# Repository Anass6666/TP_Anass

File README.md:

# TP_Anass

1.1.6 Activation de l’USART2 en mode Asynchrone : Le baud rate est réglé à 115200 bits/s par défaut.

1.2.13 Rôle de PB9 : PB9 est relié à la masse à travers une résistance pull-down. Ceci garantit que la broche reste à un niveau logique bas (0V) lorsque non connectée, évitant ainsi les états indéfinis.

1.2.14 Rôle de L1, C5 et C7 : L1 agit comme un filtre contre le bruit de haute fréquence, tandis que C5 et C7 agissent comme des condensateurs de découplage pour filtrer une large gamme de fréquences de bruit et assurer une alimentation propre et stable pour le microcontrôleur.

1.3.3 Page indiquant les valeurs des condensateurs : Les valeurs des condensateurs sont disponibles sur la page 3 du datasheet "buxxsd5wg-e".

1.3.5 Page indiquant les valeurs de condensateurs : Les valeurs des condensateurs sont répertoriées sur la page 15 du datasheet "22244B-54643".

1.3.6 Rôle de la broche CS : La broche CS est utilisée pour activer et désactiver le dispositif DAC, permettant au microcontrôleur de communiquer avec le DAC lorsque la broche est basse.

1.3.7 Rôle de la broche LDAC : La broche LDAC contrôle le moment où la sortie du DAC est mise à jour, permettant une mise à jour synchronisée de la sortie du DAC.

1.3.8 Non-utilisation du signal MISO : Le signal MISO n'est pas utilisé car le DAC est unidirectionnel et ne nécessite que des données entrantes du microcontrôleur.

1.3.10 Où trouver les indications du pinout du connecteur SWD : Les indications sont disponibles sur le lien suivant : Connecter votre débogueur.

1.4.3 Signification de 0805, 0603, 1206 : Ces chiffres font référence aux dimensions des composants électroniques en montage en surface (SMD).

1.4.4 Signification de LQFP, SOT-223, SOIC : Ces sigles désignent différents types de boîtiers utilisés pour les composants électroniques, chacun ayant ses propres caractéristiques.

3.1.4 Signification de __STATIC_INLINE : Cette directive indique au compilateur de remplacer les appels de fonction par le contenu de la fonction.

3.1.5 Présence de code dans un fichier .h : Si une fonction INLINE est définie dans un fichier d'en-tête, elle est copiée dans le fichier source lors de la compilation.

3.2.2 Valeur du prescaler : Le prescaler est réglé à 64 pour obtenir une fréquence de 250 kHz à partir d'une fréquence de 16 MHz.

3.3.3 Valeurs de PSC et de ARR : PSC est réglé à 250 et ARR à 64 pour obtenir une interruption toutes les millisecondes.

3.3.6 Localisation de la routine d'interruption : La routine de service d'interruption se trouve dans "stm3210xx_it.c".

3.3.7 Différence par rapport au code généré par la HAL : Le flag d'interruption n'est pas désactivé dans le code.

3.3.8 Impact de cette omission : L'interruption serait lancée en boucle, entraînant des problèmes de fonctionnement.

3.3.9 Solution : Il faut écrire le flag d'interruption dans la routine d'interruption.

3.4.5 Erreur dans le code : Il manque un & dans la ligne SerialTransmit(&ch,1); pour passer un pointeur sur le char.

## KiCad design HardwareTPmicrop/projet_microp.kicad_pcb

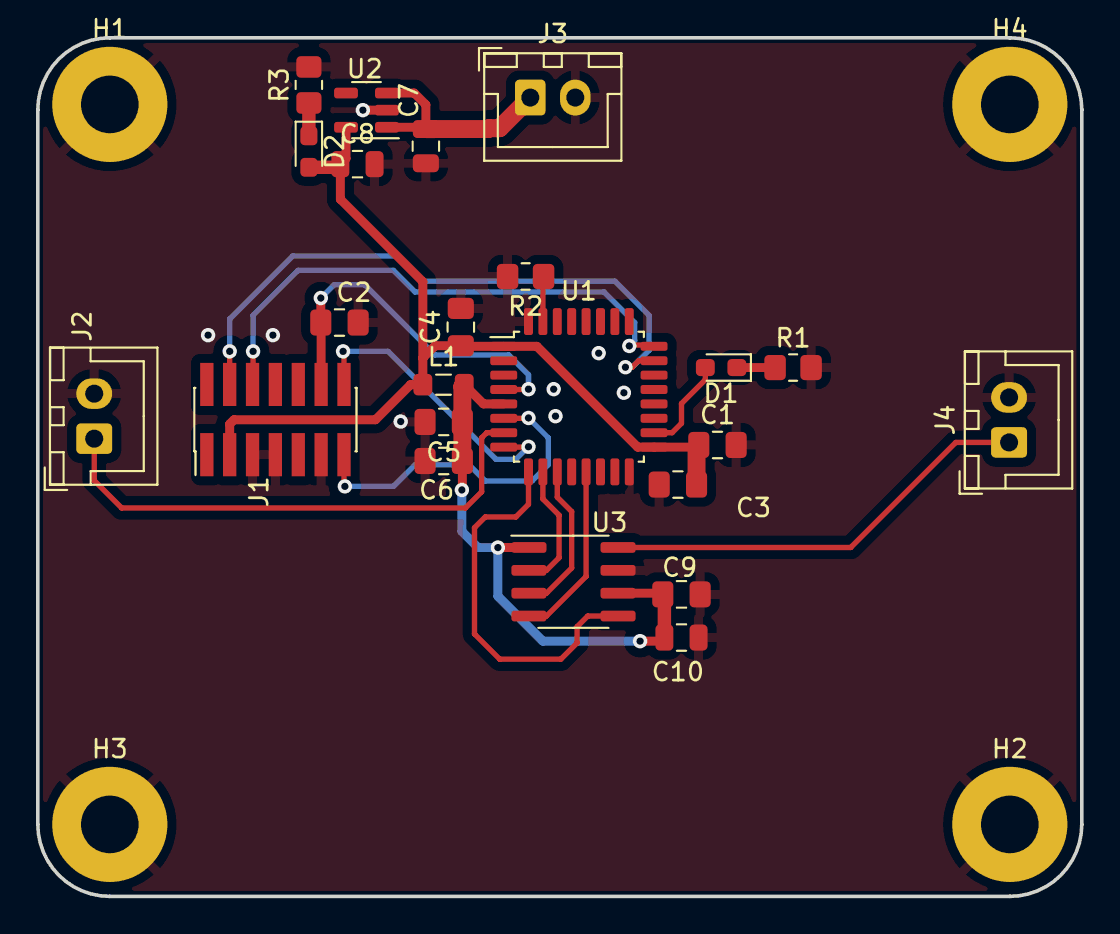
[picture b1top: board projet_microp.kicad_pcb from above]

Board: 2 copper layers, 58.0 x 47.7 mm, 27 parts (0 on the bottom side), 19 nets.

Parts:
C1: 4u7; C_0805_2012Metric_Pad1.18x1.45mm_HandSolder
C2, C3, C4, C9: 100n; C_0805_2012Metric_Pad1.18x1.45mm_HandSolder
C5: 1u; C_0805_2012Metric_Pad1.18x1.45mm_HandSolder
C6: 10n; C_0805_2012Metric_Pad1.18x1.45mm_HandSolder
C7, C8: 1uF; C_0805_2012Metric
C10: 10u; C_0805_2012Metric
D1: ORANGE TLMO1100-GS8; LED_0603_1608Metric_Pad1.05x0.95mm_HandSolder
D2: GREEN LED; LED_0603_1608Metric_Pad1.05x0.95mm_HandSolder
H1, H2, H3, H4: MountingHole_Pad; MountingHole_3.2mm_M3_Pad
J1: Conn_02x07_Odd_Even; PinHeader_2x07_P1.27mm_Vertical_SMD
J2: INPUT; JST_XH_B2B-XH-A_1x02_P2.50mm_Vertical
J3: POWER; JST_XH_B2B-XH-A_1x02_P2.50mm_Vertical
J4: OUTPUT; JST_XH_B2B-XH-A_1x02_P2.50mm_Vertical
L1: 39n; L_0805_2012Metric_Pad1.05x1.20mm_HandSolder
R1, R3: 1k; R_0805_2012Metric_Pad1.20x1.40mm_HandSolder
R2: 100k; R_0805_2012Metric_Pad1.20x1.40mm_HandSolder
U1: STM32L021K4T6; LQFP-32_7x7mm_P0.8mm
U2: BU33SD5WG-TR; SOT-23-5
U3: MCP4801-E/SN; SOIC-8_3.9x4.9mm_P1.27mm

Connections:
+3.3VA: C5.1, C6.1, C9.1, C10.1, L1.2, U1.5 (VDDA), U3.1 (Vdd), U3.6 (~SHDN)
+3V3: C1.1, C3.1, C4.1, C8.1, D2.2 (A), J1.3, L1.1, U1.1 (VDD), U1.17 (VDD), U2.5 (VOUT)
+5V: C7.1, J3.1, U2.1 (VIN), U2.3 (~SHDN)
ADC_IN1: J2.1, U1.7 (PA1)
DAC_OUT: J4.1, U3.8 (Vout)
DAC_nCS: U1.10 (PA4), U3.2 (~CS)
DAC_nLDAC: U1.9 (PA3), U3.5 (~LDAC)
GND: C1.2, C2.2, C3.2, C4.2, C5.2, C6.2, C7.2, C8.2, C9.2, C10.2, H1.1, H2.1, H3.1, H4.1, J1.5, J1.7, J1.11, J2.2, J3.2, J4.2, R1.2, R2.2, R3.2, U1.16 (VSS), U1.32 (VSS), U2.2 (GND), U3.7 (Vss)
LED_STATUS: D1.2 (A), U1.18 (PA8)
NRST: C2.1, J1.12, U1.4 (NRST)
unnamed: D1.1 (K), R1.1
unnamed: D2.1 (K), R3.1
unnamed: R2.1, U1.31 (PB9)
SPI1_MOSI: U1.13 (PA7), U3.4 (SDI)
SPI1_SCK: U1.11 (PA5), U3.3 (SCK)
SWDCK: J1.6, U1.24 (PA14)
SWDIO: J1.4, U1.23 (PA13)
USART2_RX: J1.13, U1.6 (PA0)
USART2_TX: J1.14, U1.8 (PA2)

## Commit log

2024-03-23 SALUT
